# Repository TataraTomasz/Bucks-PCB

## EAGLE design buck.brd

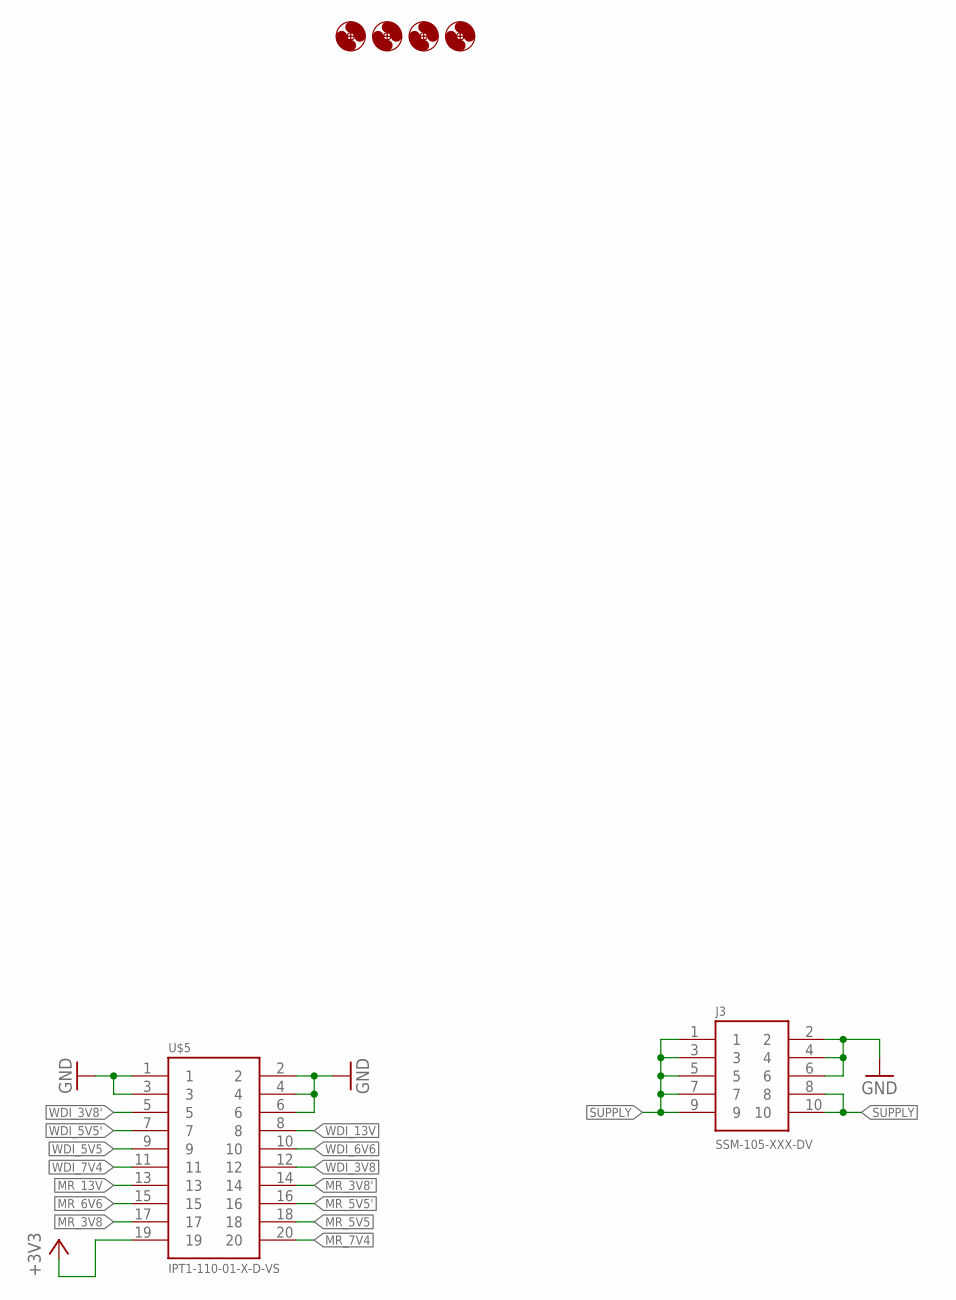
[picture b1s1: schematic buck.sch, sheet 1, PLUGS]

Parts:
H1, H2, H3, H4: MOUNT-HOLE3.2; 3,2
J3: SSM-105-XXX-DV
U$5: IPT1-110-01-X-D-VS

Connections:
+3V3: U$5.19; also elsewhere on the board
GND: J3.2, J3.4, J3.6, U$5.1, U$5.2, U$5.3, U$5.4, U$5.6; also elsewhere on the board
MR_3V8: U$5.17; also elsewhere on the board
MR_3V8': U$5.14; also elsewhere on the board
MR_5V5: U$5.18; also elsewhere on the board
MR_5V5': U$5.16; also elsewhere on the board
MR_6V6: U$5.15; also elsewhere on the board
MR_7V4: U$5.20; also elsewhere on the board
MR_13V: U$5.13; also elsewhere on the board
SUPPLY: J3.1, J3.3, J3.5, J3.7, J3.8, J3.9, J3.10; also elsewhere on the board
WDI_3V8: U$5.12; also elsewhere on the board
WDI_3V8': U$5.5; also elsewhere on the board
WDI_5V5: U$5.9; also elsewhere on the board
WDI_5V5': U$5.7; also elsewhere on the board
WDI_6V6: U$5.10; also elsewhere on the board
WDI_7V4: U$5.11; also elsewhere on the board
WDI_13V: U$5.8; also elsewhere on the board

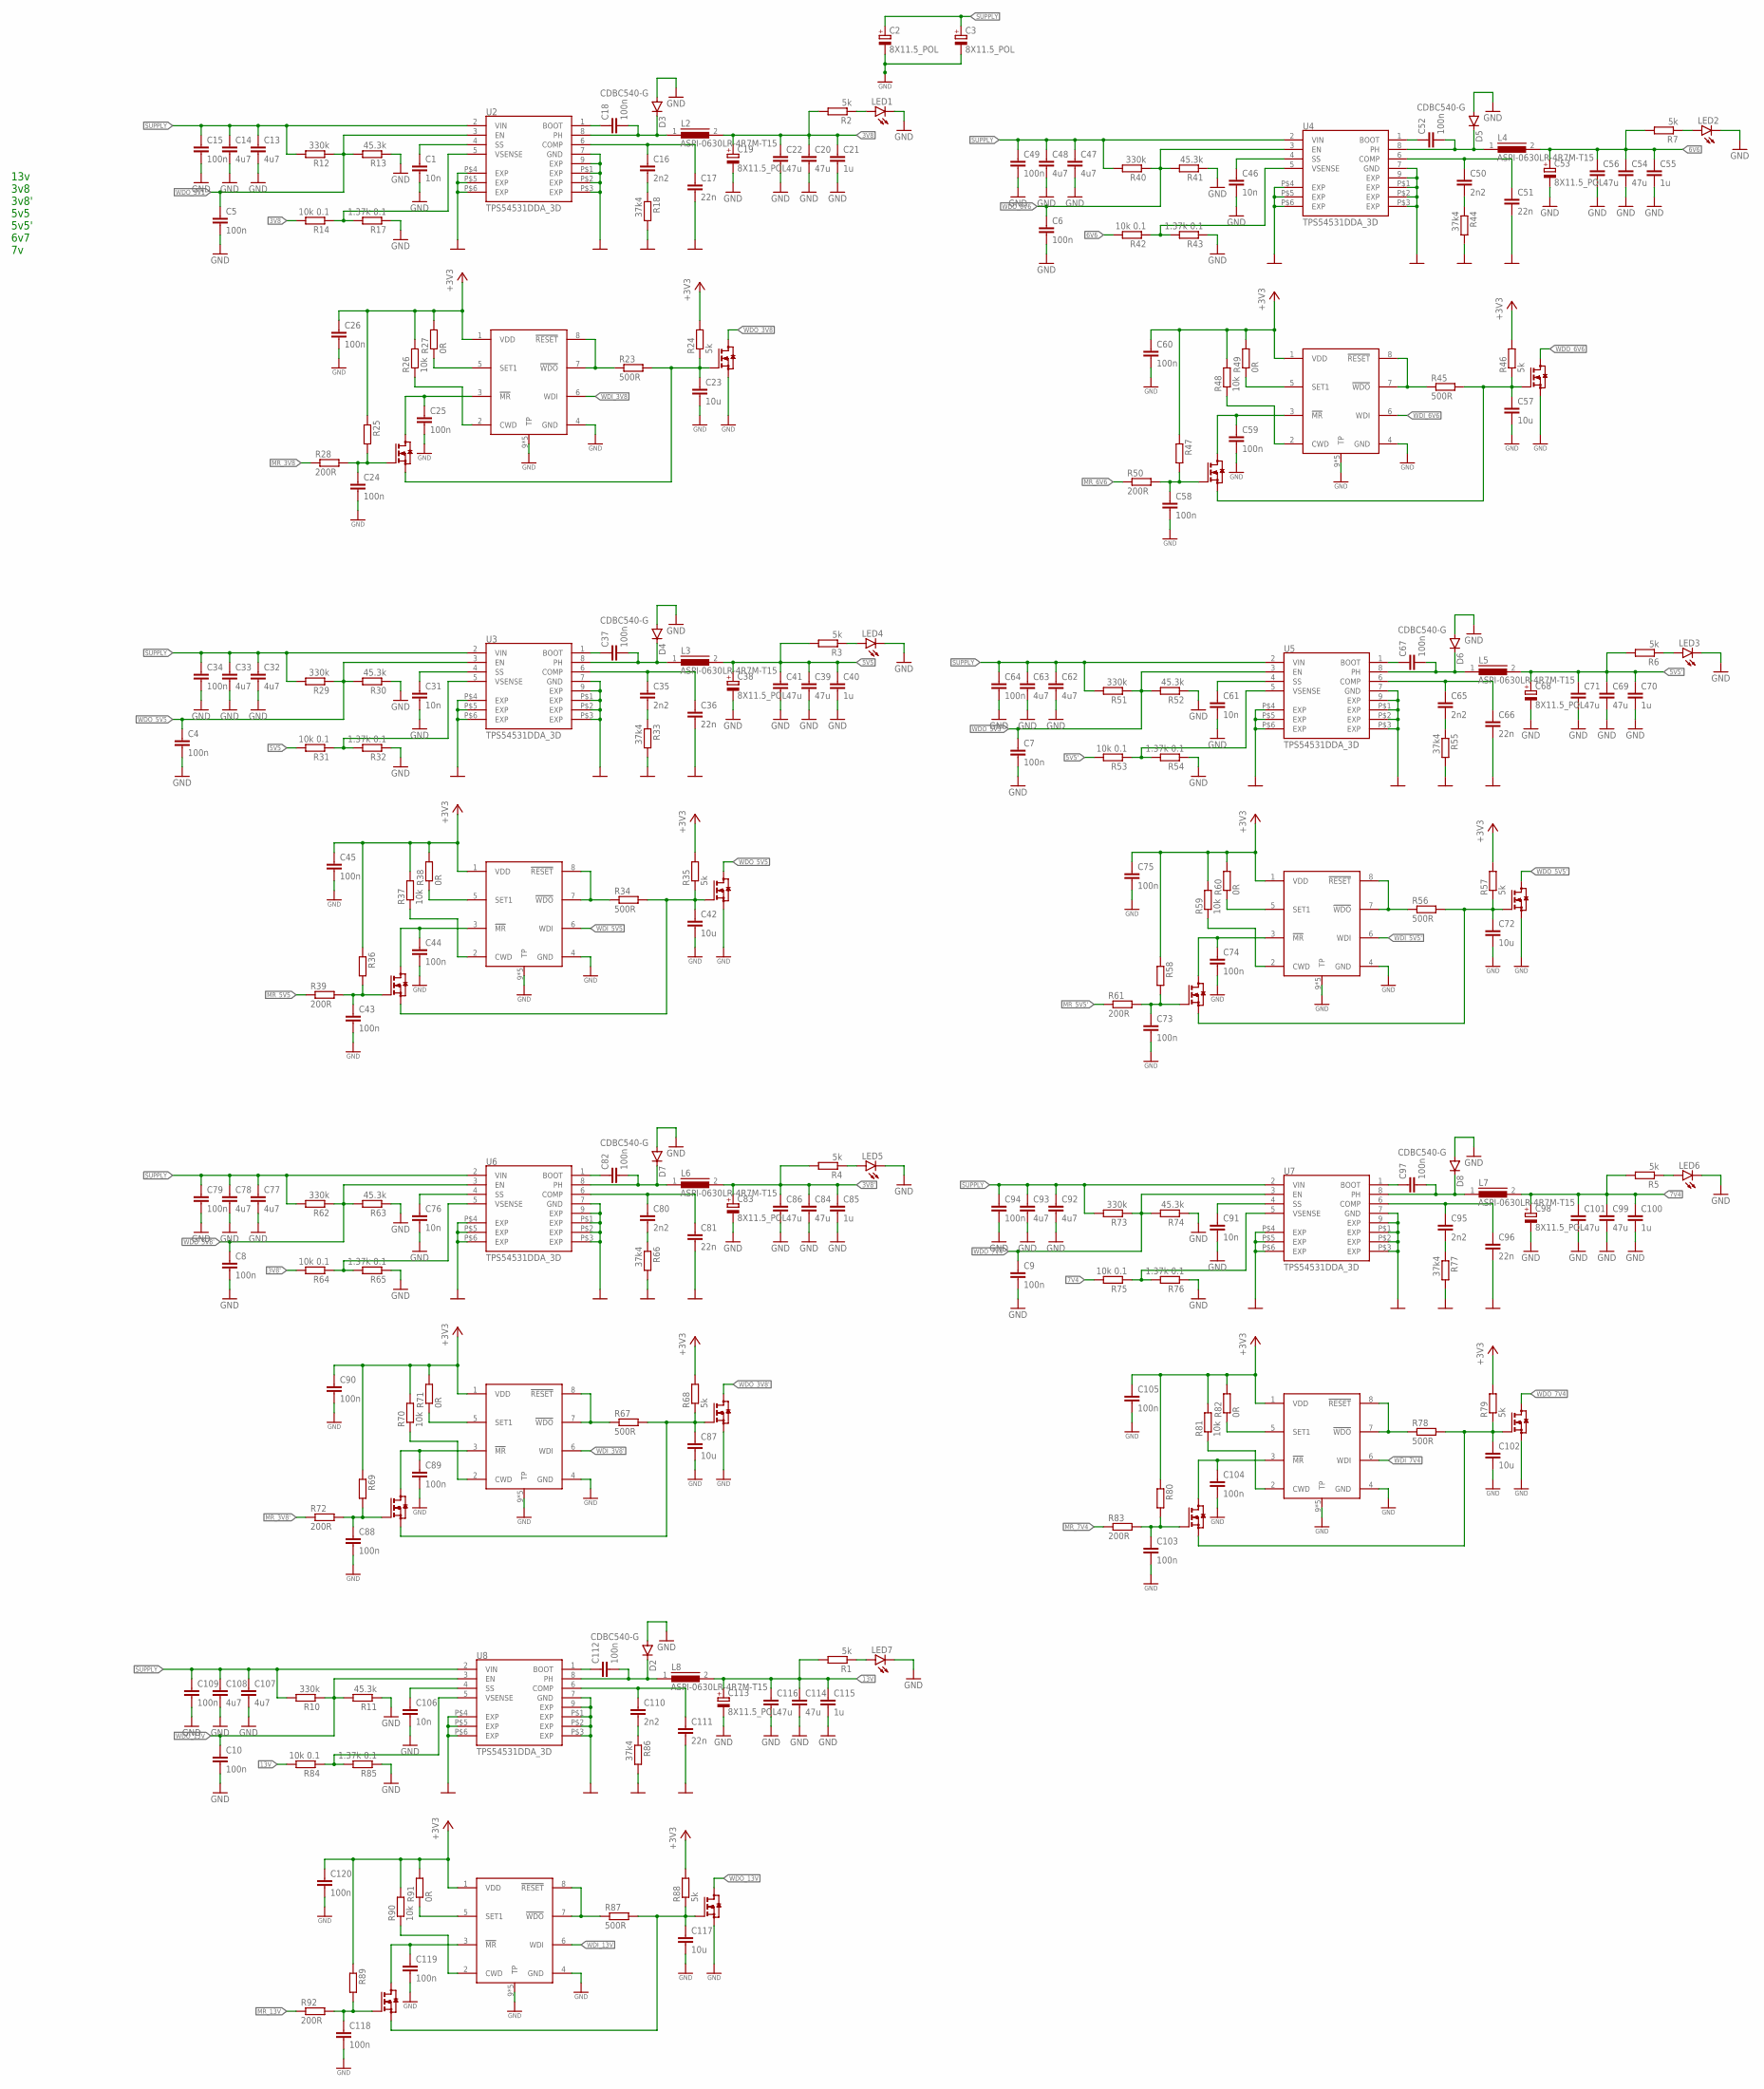
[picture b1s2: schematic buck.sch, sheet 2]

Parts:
C1, C31, C46, C61, C76, C91, C106: 10n; C0603K
C2, C3, C19, C38, C53, C68, C83, C98, C113: 8X11.5_POL; CAPPRD350W65D800H1150A
C4, C5, C6, C7, C8, C9, C10, C15, C18, C24, C25, C26, C34, C37, C43, C44, C45, C49, C52, C58, C59, C60, C64, C67, C73, C74, C75, C79, C82, C88, C89, C90, C94, C97, C103, C104, C105, C109, C112, C118, C119, C120: 100n; C0603K
C13, C14, C32, C33, C47, C48, C62, C63, C77, C78, C92, C93, C107, C108: 4u7; C0805K
C16, C35, C50, C65, C80, C95, C110: 2n2; C0603K
C17, C36, C51, C66, C81, C96, C111: 22n; C0603K
C20, C22, C39, C41, C54, C56, C69, C71, C84, C86, C99, C101, C114, C116: 47u; C1210
C21, C40, C55, C70, C85, C100, C115: 1u; C0603K
C23, C42, C57, C72, C87, C102, C117: 10u; C0805K
D2, D3, D4, D5, D6, D7, D8: CDBC540-G; SMC
L2, L3, L4, L5, L6, L7, L8: ASPI-0630LR-4R7M-T15; DR74
LED1, LED2, LED3, LED4, LED5, LED6, LED7: LEDCHIPLED_0603; CHIPLED_0603
Q1, Q2, Q5, Q6, Q7, Q8, Q9, Q10, Q11, Q12, Q13, Q14, Q15, Q16: BSS123; SOT23
R1, R2, R3, R4, R5, R6, R7, R24, R35, R46, R57, R68, R79, R88: 5k; R0603
R10, R12, R29, R40, R51, R62, R73: 330k; R0603
R11, R13, R30, R41, R52, R63, R74: 45.3k; R0603
R14, R31, R42, R53, R64, R75, R84: 10k 0.1; R0603
R17, R32, R43, R54, R65, R76, R85: 1.37k 0.1; R0603
R18, R33, R44, R55, R66, R77, R86: 37k4; R0603
R23, R34, R45, R56, R67, R78, R87: 500R; R0603
R25, R36, R47, R58, R69, R80, R89: R-EU_R0603; R0603
R26, R37, R48, R59, R70, R81, R90: 10k; R0603
R27, R38, R49, R60, R71, R82, R91: 0R; R0603
R28, R39, R50, R61, R72, R83, R92: 200R; R0603
U2, U3, U4, U5, U6, U7, U8: TPS54531DDA_3D; SOIC127P600X150-9T240X310
U$6, U$7, U$8, U$9, U$10, U$11, U$12: TPS3852; SON65P300X300X100-9N

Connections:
3V8: C19.1 (+), C20.1, C21.1, C22.1, L2.2, R2.2, R14.2; also elsewhere on the board
3V8': C83.1 (+), C84.1, C85.1, C86.1, L6.2, R4.2, R64.2; also elsewhere on the board
5V5: C38.1 (+), C39.1, C40.1, C41.1, L3.2, R3.2, R31.2; also elsewhere on the board
5V5': C68.1 (+), C69.1, C70.1, C71.1, L5.2, R6.2, R53.2; also elsewhere on the board
6V6: C53.1 (+), C54.1, C55.1, C56.1, L4.2, R7.2, R42.2; also elsewhere on the board
7V4: C98.1 (+), C99.1, C100.1, C101.1, L7.2, R5.2, R75.2; also elsewhere on the board
13V: C113.1 (+), C114.1, C115.1, C116.1, L8.2, R1.2, R84.2; also elsewhere on the board
+3V3: C26.1, C45.1, C60.1, C75.1, C90.1, C105.1, C120.1, R24.2, R25.1, R26.2, R27.2, R35.2, R36.1, R37.2, R38.2, R46.2, R47.1, R48.2, R49.2, R57.2, R58.1, R59.2, R60.2, R68.2, R69.1, R70.2, R71.2, R79.2, R80.1, R81.2, R82.2, R88.2, R89.1, R90.2, R91.2, U$6.1 (VDD), U$7.1 (VDD), U$8.1 (VDD), U$9.1 (VDD), U$10.1 (VDD), U$11.1 (VDD), U$12.1 (VDD); also elsewhere on the board
ENABLE2: C24.1, Q2.1 (G), R25.2, R28.2
ENABLE3: C43.1, Q6.1 (G), R36.2, R39.2
ENABLE4: C58.1, Q8.1 (G), R47.2, R50.2
ENABLE5: C73.1, Q10.1 (G), R58.2, R61.2
ENABLE6: C88.1, Q12.1 (G), R69.2, R72.2
ENABLE7: C103.1, Q14.1 (G), R80.2, R83.2
ENABLE8: C118.1, Q16.1 (G), R89.2, R92.2
GND: C1.2, C2.2 (-), C3.2 (-), C4.2, C5.2, C6.2, C7.2, C8.2, C9.2, C10.2, C13.2, C14.2, C15.2, C17.2, C19.2 (-), C20.2, C21.2, C22.2, C23.2, C24.2, C25.2, C26.2, C31.2, C32.2, C33.2, C34.2, C36.2, C38.2 (-), C39.2, C40.2, C41.2, C42.2, C43.2, C44.2, C45.2, C46.2, C47.2, C48.2, C49.2, C51.2, C53.2 (-), C54.2, C55.2, C56.2, C57.2, C58.2, C59.2, C60.2, C61.2, C62.2, C63.2, C64.2, C66.2, C68.2 (-), C69.2, C70.2, C71.2, C72.2, C73.2, C74.2, C75.2, C76.2, C77.2, C78.2, C79.2, C81.2, C83.2 (-), C84.2, C85.2, C86.2, C87.2, C88.2, C89.2, C90.2, C91.2, C92.2, C93.2, C94.2, C96.2, C98.2 (-), C99.2, C100.2, C101.2, C102.2, C103.2, C104.2, C105.2, C106.2, C107.2, C108.2, C109.2, C111.2, C113.2 (-), C114.2, C115.2, C116.2, C117.2, C118.2, C119.2, C120.2, D2.A, D3.A, D4.A, D5.A, D6.A, D7.A, D8.A, LED1.C, LED2.C, LED3.C, LED4.C, LED5.C, LED6.C, LED7.C, Q1.2 (S), Q5.2 (S), Q7.2 (S), Q9.2 (S), Q11.2 (S), Q13.2 (S), Q15.2 (S), R11.1, R13.1, R17.1, R18.2, R30.1, R32.1, R33.2, R41.1, R43.1, R44.2, R52.1, R54.1, R55.2, R63.1, R65.1, R66.2, R74.1, R76.1, R77.2, R85.1, R86.2, U2.7 (GND), U2.9 (EXP), U2.P$1 (EXP), U2.P$2 (EXP), U2.P$3 (EXP), U2.P$4 (EXP), U2.P$5 (EXP), U2.P$6 (EXP), U3.7 (GND), U3.9 (EXP), U3.P$1 (EXP), U3.P$2 (EXP), U3.P$3 (EXP), U3.P$4 (EXP), U3.P$5 (EXP), U3.P$6 (EXP), U4.7 (GND), U4.9 (EXP), U4.P$1 (EXP), U4.P$2 (EXP), U4.P$3 (EXP), U4.P$4 (EXP), U4.P$5 (EXP), U4.P$6 (EXP), U5.7 (GND), U5.9 (EXP), U5.P$1 (EXP), U5.P$2 (EXP), U5.P$3 (EXP), U5.P$4 (EXP), U5.P$5 (EXP), U5.P$6 (EXP), U6.7 (GND), U6.9 (EXP), U6.P$1 (EXP), U6.P$2 (EXP), U6.P$3 (EXP), U6.P$4 (EXP), U6.P$5 (EXP), U6.P$6 (EXP), U7.7 (GND), U7.9 (EXP), U7.P$1 (EXP), U7.P$2 (EXP), U7.P$3 (EXP), U7.P$4 (EXP), U7.P$5 (EXP), U7.P$6 (EXP), U8.7 (GND), U8.9 (EXP), U8.P$1 (EXP), U8.P$2 (EXP), U8.P$3 (EXP), U8.P$4 (EXP), U8.P$5 (EXP), U8.P$6 (EXP), U$6.4 (GND), U$6.9 (TP), U$6.9_1 (TP), U$6.9_2 (TP), U$6.9_3 (TP), U$6.9_4 (TP), U$7.4 (GND), U$7.9 (TP), U$7.9_1 (TP), U$7.9_2 (TP), U$7.9_3 (TP), U$7.9_4 (TP), U$8.4 (GND), U$8.9 (TP), U$8.9_1 (TP), U$8.9_2 (TP), U$8.9_3 (TP), U$8.9_4 (TP), U$9.4 (GND), U$9.9 (TP), U$9.9_1 (TP), U$9.9_2 (TP), U$9.9_3 (TP), U$9.9_4 (TP), U$10.4 (GND), U$10.9 (TP), U$10.9_1 (TP), U$10.9_2 (TP), U$10.9_3 (TP), U$10.9_4 (TP), U$11.4 (GND), U$11.9 (TP), U$11.9_1 (TP), U$11.9_2 (TP), U$11.9_3 (TP), U$11.9_4 (TP), U$12.4 (GND), U$12.9 (TP), U$12.9_1 (TP), U$12.9_2 (TP), U$12.9_3 (TP), U$12.9_4 (TP); also elsewhere on the board
MAIN_SUPPLY_DIS2: C23.1, Q1.1 (G), Q2.2 (S), R23.2, R24.1
MAIN_SUPPLY_DIS3: C42.1, Q5.1 (G), Q6.2 (S), R34.2, R35.1
MAIN_SUPPLY_DIS4: C57.1, Q7.1 (G), Q8.2 (S), R45.2, R46.1
MAIN_SUPPLY_DIS5: C72.1, Q9.1 (G), Q10.2 (S), R56.2, R57.1
MAIN_SUPPLY_DIS6: C87.1, Q11.1 (G), Q12.2 (S), R67.2, R68.1
MAIN_SUPPLY_DIS7: C102.1, Q13.1 (G), Q14.2 (S), R78.2, R79.1
MAIN_SUPPLY_DIS8: C117.1, Q15.1 (G), Q16.2 (S), R87.2, R88.1
MR_3V8: R28.1; also elsewhere on the board
MR_3V8': R72.1; also elsewhere on the board
MR_5V5: R39.1; also elsewhere on the board
MR_5V5': R61.1; also elsewhere on the board
MR_6V6: R50.1; also elsewhere on the board
MR_7V4: R83.1; also elsewhere on the board
MR_13V: R92.1; also elsewhere on the board
unnamed: LED7.A, R1.1
unnamed: LED1.A, R2.1
unnamed: LED4.A, R3.1
unnamed: LED5.A, R4.1
unnamed: LED6.A, R5.1
unnamed: LED3.A, R6.1
unnamed: LED2.A, R7.1
unnamed: R84.1, R85.2, U8.5 (VSENSE)
unnamed: R14.1, R17.2, U2.5 (VSENSE)
unnamed: C1.1, U2.4 (SS)
unnamed: C16.1, C17.1, U2.6 (COMP)
unnamed: C16.2, R18.1
unnamed: C18.1, U2.1 (BOOT)
unnamed: C18.2, D3.C, L2.1, U2.8 (PH)
unnamed: R23.1, U$6.7 (!WDO), U$6.8 (!RESET)
unnamed: C25.1, Q2.3 (D), U$6.3 (!MR)
unnamed: R26.1, U$6.2 (CWD)
unnamed: R27.1, U$6.5 (SET1)
unnamed: C106.1, U8.4 (SS)
unnamed: R31.1, R32.2, U3.5 (VSENSE)
unnamed: C31.1, U3.4 (SS)
unnamed: C35.1, C36.1, U3.6 (COMP)
unnamed: C35.2, R33.1
unnamed: C37.1, U3.1 (BOOT)
unnamed: C37.2, D4.C, L3.1, U3.8 (PH)
unnamed: R34.1, U$7.7 (!WDO), U$7.8 (!RESET)
unnamed: C44.1, Q6.3 (D), U$7.3 (!MR)
unnamed: R37.1, U$7.2 (CWD)
unnamed: R38.1, U$7.5 (SET1)
unnamed: R42.1, R43.2, U4.5 (VSENSE)
unnamed: C46.1, U4.4 (SS)
unnamed: C50.1, C51.1, U4.6 (COMP)
unnamed: C50.2, R44.1
unnamed: C52.1, U4.1 (BOOT)
unnamed: C52.2, D5.C, L4.1, U4.8 (PH)
unnamed: R45.1, U$8.7 (!WDO), U$8.8 (!RESET)
unnamed: C59.1, Q8.3 (D), U$8.3 (!MR)
unnamed: R48.1, U$8.2 (CWD)
unnamed: R49.1, U$8.5 (SET1)
unnamed: R53.1, R54.2, U5.5 (VSENSE)
unnamed: C61.1, U5.4 (SS)
unnamed: C65.1, C66.1, U5.6 (COMP)
unnamed: C65.2, R55.1
unnamed: C67.1, U5.1 (BOOT)
unnamed: C67.2, D6.C, L5.1, U5.8 (PH)
unnamed: R56.1, U$9.7 (!WDO), U$9.8 (!RESET)
unnamed: C74.1, Q10.3 (D), U$9.3 (!MR)
unnamed: R59.1, U$9.2 (CWD)
unnamed: R60.1, U$9.5 (SET1)
unnamed: R64.1, R65.2, U6.5 (VSENSE)
unnamed: C76.1, U6.4 (SS)
unnamed: C80.1, C81.1, U6.6 (COMP)
unnamed: C80.2, R66.1
unnamed: C82.1, U6.1 (BOOT)
unnamed: C82.2, D7.C, L6.1, U6.8 (PH)
unnamed: R67.1, U$10.7 (!WDO), U$10.8 (!RESET)
unnamed: C89.1, Q12.3 (D), U$10.3 (!MR)
unnamed: R70.1, U$10.2 (CWD)
unnamed: R71.1, U$10.5 (SET1)
unnamed: R75.1, R76.2, U7.5 (VSENSE)
unnamed: C91.1, U7.4 (SS)
unnamed: C95.1, C96.1, U7.6 (COMP)
unnamed: C95.2, R77.1
unnamed: C97.1, U7.1 (BOOT)
unnamed: C97.2, D8.C, L7.1, U7.8 (PH)
unnamed: R78.1, U$11.7 (!WDO), U$11.8 (!RESET)
unnamed: C104.1, Q14.3 (D), U$11.3 (!MR)
unnamed: R81.1, U$11.2 (CWD)
unnamed: R82.1, U$11.5 (SET1)
unnamed: C110.1, C111.1, U8.6 (COMP)
unnamed: C110.2, R86.1
unnamed: C112.1, U8.1 (BOOT)
unnamed: C112.2, D2.C, L8.1, U8.8 (PH)
unnamed: R87.1, U$12.7 (!WDO), U$12.8 (!RESET)
unnamed: C119.1, Q16.3 (D), U$12.3 (!MR)
unnamed: R90.1, U$12.2 (CWD)
unnamed: R91.1, U$12.5 (SET1)
SUPPLY: C2.1 (+), C3.1 (+), C13.1, C14.1, C15.1, C32.1, C33.1, C34.1, C47.1, C48.1, C49.1, C62.1, C63.1, C64.1, C77.1, C78.1, C79.1, C92.1, C93.1, C94.1, C107.1, C108.1, C109.1, R10.2, R12.2, R29.2, R40.2, R51.2, R62.2, R73.2, U2.2 (VIN), U3.2 (VIN), U4.2 (VIN), U5.2 (VIN), U6.2 (VIN), U7.2 (VIN), U8.2 (VIN); also elsewhere on the board
WDI_3V8: U$6.6 (WDI); also elsewhere on the board
WDI_3V8': U$10.6 (WDI); also elsewhere on the board
WDI_5V5: U$7.6 (WDI); also elsewhere on the board
WDI_5V5': U$9.6 (WDI); also elsewhere on the board
WDI_6V6: U$8.6 (WDI); also elsewhere on the board
WDI_7V4: U$11.6 (WDI); also elsewhere on the board
WDI_13V: U$12.6 (WDI); also elsewhere on the board
WDO_3V8: Q1.3 (D)
WDO_3V8': C8.1, Q11.3 (D), R62.1, R63.2, U6.3 (EN)
WDO_5V1: C5.1, R12.1, R13.2, U2.3 (EN)
WDO_5V5: C4.1, Q5.3 (D), R29.1, R30.2, U3.3 (EN)
WDO_5V5': C7.1, Q9.3 (D), R51.1, R52.2, U5.3 (EN)
WDO_6V6: C6.1, Q7.3 (D), R40.1, R41.2, U4.3 (EN)
WDO_7V4: C9.1, Q13.3 (D), R73.1, R74.2, U7.3 (EN)
WDO_13V: C10.1, Q15.3 (D), R10.1, R11.2, U8.3 (EN)

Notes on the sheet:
13v 3v8 3v8' 5v5 5v5' 6v7 7v

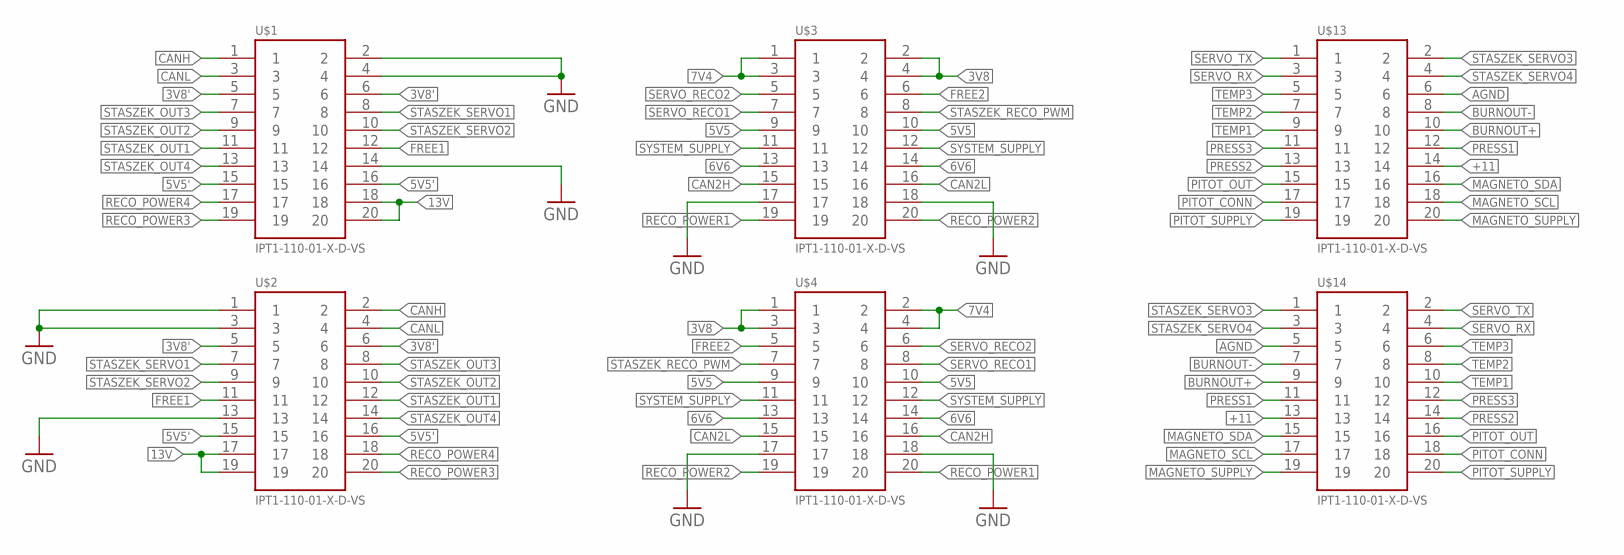
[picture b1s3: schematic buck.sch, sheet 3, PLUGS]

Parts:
U$1, U$2, U$3, U$4, U$13, U$14: IPT1-110-01-X-D-VS

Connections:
3V8: U$3.2, U$3.4, U$4.1, U$4.3; also elsewhere on the board
3V8': U$1.5, U$1.6, U$2.5, U$2.6; also elsewhere on the board
5V5: U$3.9, U$3.10, U$4.9, U$4.10; also elsewhere on the board
5V5': U$1.15, U$1.16, U$2.15, U$2.16; also elsewhere on the board
6V6: U$3.13, U$3.14, U$4.13, U$4.14; also elsewhere on the board
7V4: U$3.1, U$3.3, U$4.2, U$4.4; also elsewhere on the board
13V: U$1.18, U$1.20, U$2.17, U$2.19; also elsewhere on the board
+11: U$13.14, U$14.13
AGND: U$13.6, U$14.5
BURNOUT+: U$13.10, U$14.9
BURNOUT-: U$13.8, U$14.7
CAN2H: U$3.15, U$4.16
CAN2L: U$3.16, U$4.15
CANH: U$1.1, U$2.2
CANL: U$1.3, U$2.4
FREE1: U$1.12, U$2.11
FREE2: U$3.6, U$4.5
GND: U$1.2, U$1.4, U$1.14, U$2.1, U$2.3, U$2.13, U$3.17, U$3.18, U$4.17, U$4.18; also elsewhere on the board
MAGNETO_SCL: U$13.18, U$14.17
MAGNETO_SDA: U$13.16, U$14.15
MAGNETO_SUPPLY: U$13.20, U$14.19
PITOT_CONN: U$13.17, U$14.18
PITOT_OUT: U$13.15, U$14.16
PITOT_SUPPLY: U$13.19, U$14.20
PRESS1: U$13.12, U$14.11
PRESS2: U$13.13, U$14.14
PRESS3: U$13.11, U$14.12
RECO_POWER1: U$3.19, U$4.20
RECO_POWER2: U$3.20, U$4.19
RECO_POWER3: U$1.19, U$2.20
RECO_POWER4: U$1.17, U$2.18
SERVO_RECO1: U$3.7, U$4.8
SERVO_RECO2: U$3.5, U$4.6
SERVO_RX: U$13.3, U$14.4
SERVO_TX: U$13.1, U$14.2
STASZEK_OUT1: U$1.11, U$2.12
STASZEK_OUT2: U$1.9, U$2.10
STASZEK_OUT3: U$1.7, U$2.8
STASZEK_OUT4: U$1.13, U$2.14
STASZEK_RECO_PWM: U$3.8, U$4.7
STASZEK_SERVO1: U$1.8, U$2.7
STASZEK_SERVO2: U$1.10, U$2.9
STASZEK_SERVO3: U$13.2, U$14.1
STASZEK_SERVO4: U$13.4, U$14.3
SYSTEM_SUPPLY: U$3.11, U$3.12, U$4.11, U$4.12
TEMP1: U$13.9, U$14.10
TEMP2: U$13.7, U$14.8
TEMP3: U$13.5, U$14.6

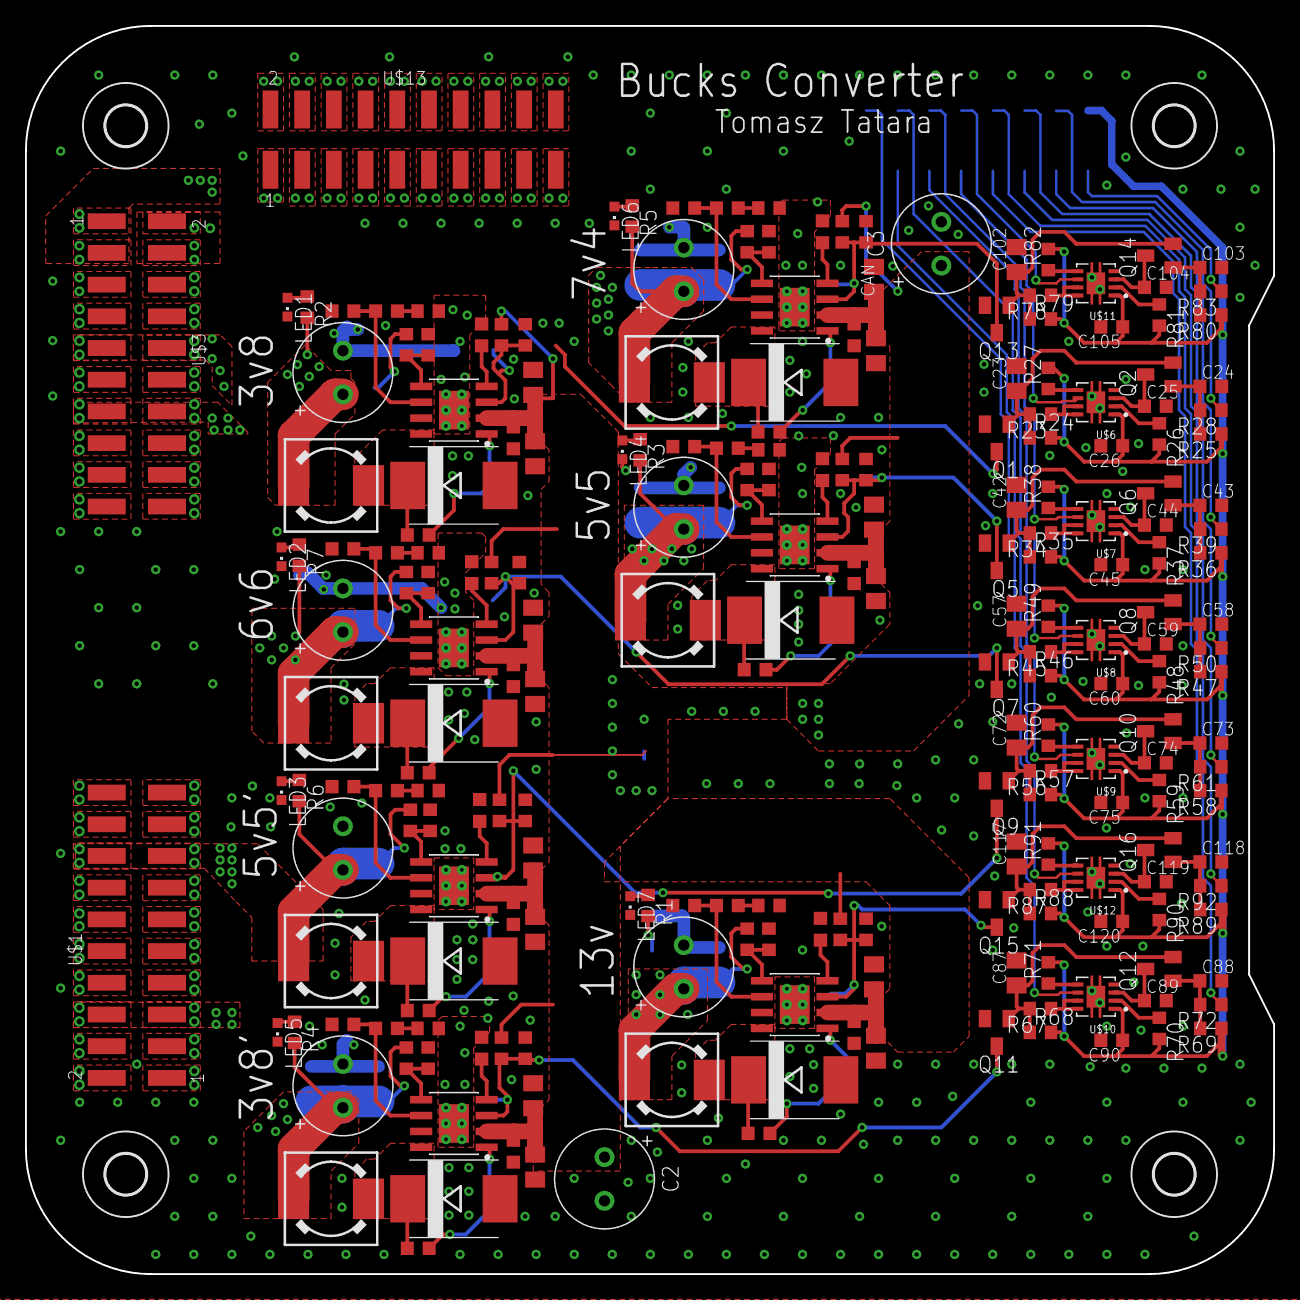
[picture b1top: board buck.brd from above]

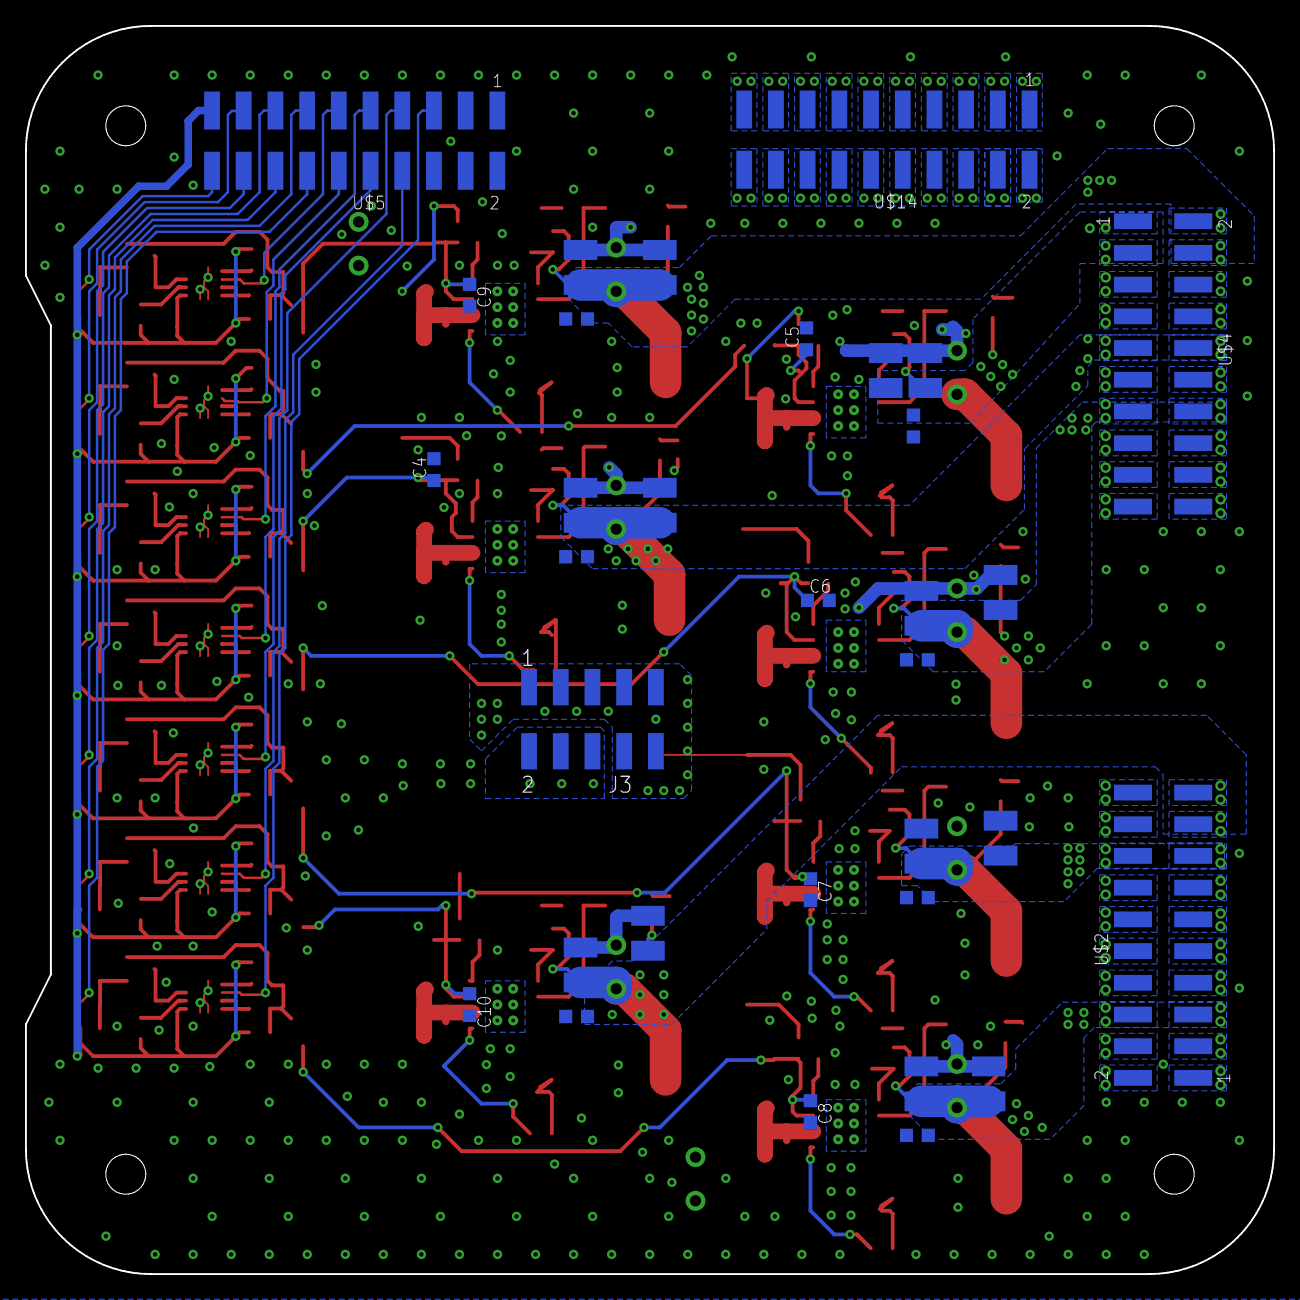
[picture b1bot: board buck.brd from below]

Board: 2 copper layers, 100.0 x 100.0 mm, 259 parts (33 on the bottom side), 162 nets.

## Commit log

2019-03-09 commit before Bucks graph
2019-03-09 final version v1.0
2019-04-18 version 2 for production

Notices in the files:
parts and their libraries:
SparkFun-Aesthetics: Licensing: CC v3.0 Share-Alike You are welcome to use this library for commercial purposes.
